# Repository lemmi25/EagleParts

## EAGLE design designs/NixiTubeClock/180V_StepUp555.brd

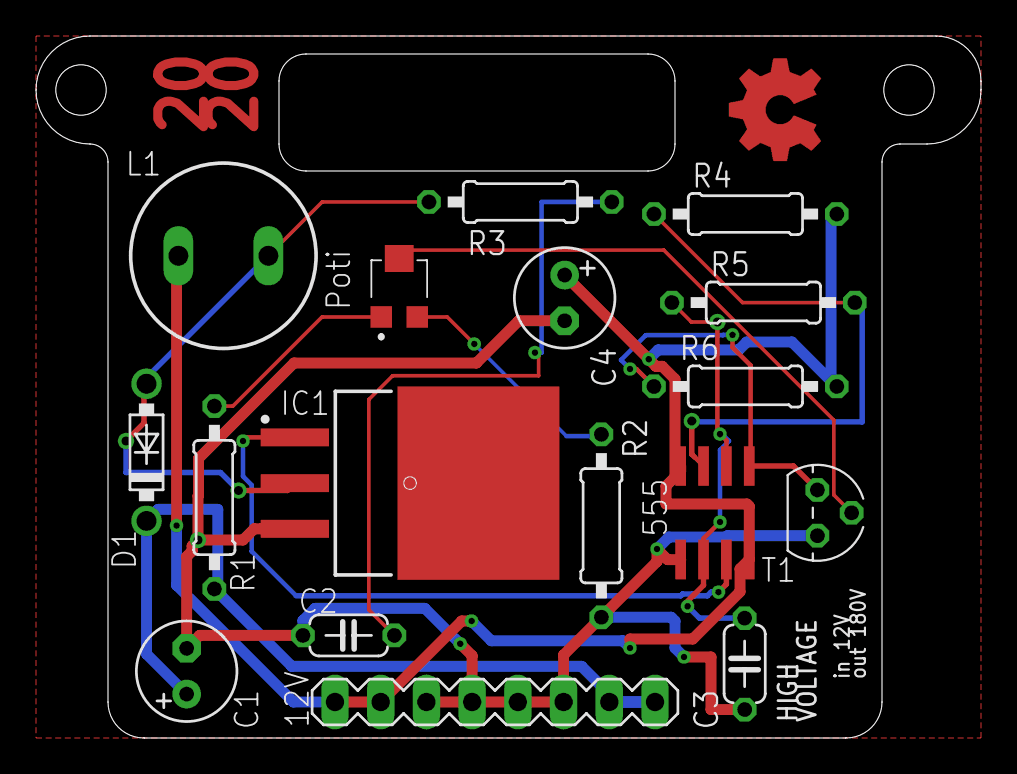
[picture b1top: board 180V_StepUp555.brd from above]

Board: 2 copper layers, 52.5 x 39.0 mm, 17 parts (0 on the bottom side), 12 nets.

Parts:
C1: 2.2uF; E2,5-6
C2: 100pF; C050-024X044
C3: 222; C050-024X044
C4: 330uF; E2,5-6
D1: UF4004; DO41-7.6
IC1: IRF740SPBF; TO254P1524X483-4N
IC2: LM555D; SO08
L1: SD12K100
R1: 220k; 0207/10
R2: 470R; 0207/10
R3: 2.2k; 0207/10
R4: 1k; 0207/10
R5: 10k; 0207/10
R6: 56k; 0207/10
SV2: MA08-1
T1: BC547; TO92
VR1: 1K; EVM3YSX50B14

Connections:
12V: C4.+, IC2.4, IC2.8, L1.2, R4.2, R6.2, SV2.1, SV2.2
+170V: C1.+, D1.C, R1.2, SV2.7, SV2.8
GND: C1.-, C2.2, C3.2, C4.-, IC1.3, IC2.1, R2.1, SV2.3, SV2.4, SV2.5, SV2.6, T1.1
unnamed: R2.2, VR1.C1
unnamed: R1.1, VR1.A1
unnamed: T1.2, VR1.B1
unnamed: D1.A, IC1.2, L1.1, R3.2
unnamed: IC2.5, R6.1, T1.3
unnamed: C2.1, R3.1
unnamed: C3.1, IC2.2, IC2.6, R5.1
unnamed: IC2.7, R4.1, R5.2
unnamed: IC1.1, IC2.3

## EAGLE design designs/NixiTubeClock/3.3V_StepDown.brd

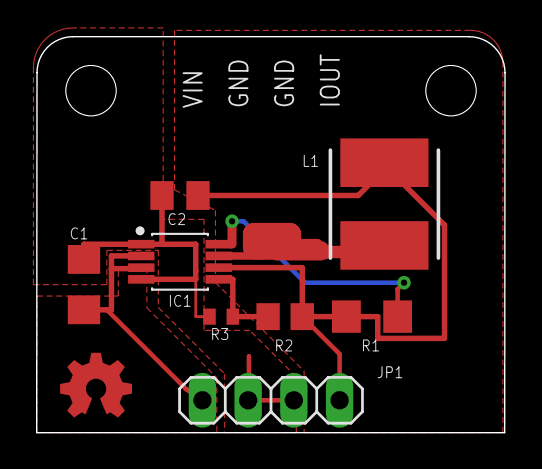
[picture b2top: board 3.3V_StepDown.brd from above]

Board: 2 copper layers, 26.0 x 22.0 mm, 8 parts (0 on the bottom side), 6 nets.

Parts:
C1: 10uF; C1206
C2: 22uF; C0805K
IC1: TPS62160DGKR; SOP65P490X110-8N
JP1: 1X04
L1: VLS6045EX-221M; INDPM6060X450N
R1: 100kOhm; R1206
R2: 562kOhm; R0805
R3: 180kOhm; R0402

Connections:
AGND: C1.2, C2.2, IC1.1, IC1.4, JP1.2, JP1.3, R3.1
FB2: IC1.5, R2.1, R3.2
IOUT: C2.1, IC1.6, JP1.4, L1.2, R1.2, R2.2
PG2: IC1.8, R1.1
SW2: IC1.7, L1.1
VIN: C1.1, IC1.2, IC1.3, JP1.1

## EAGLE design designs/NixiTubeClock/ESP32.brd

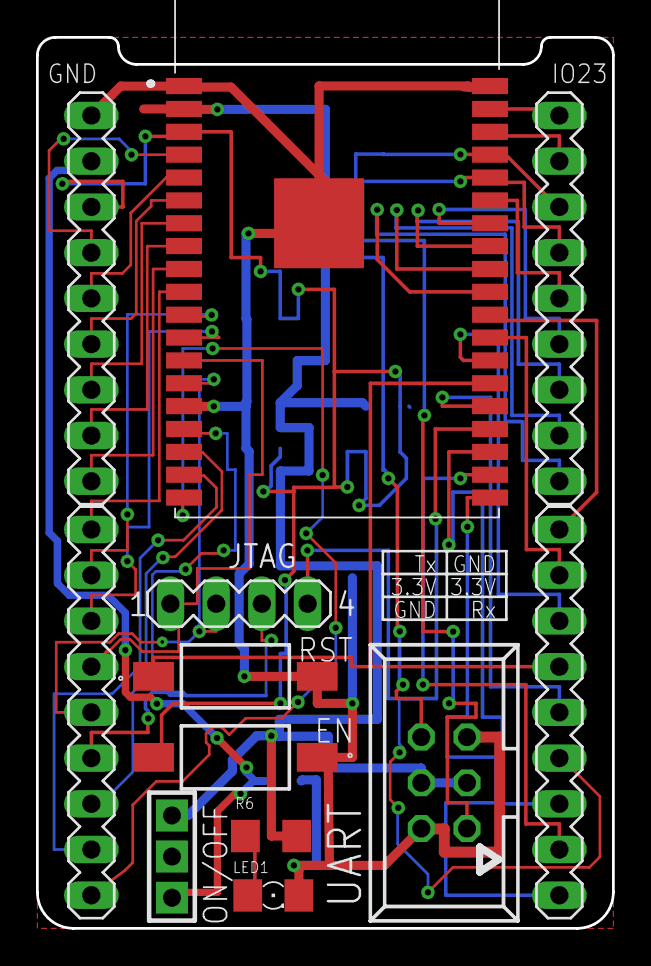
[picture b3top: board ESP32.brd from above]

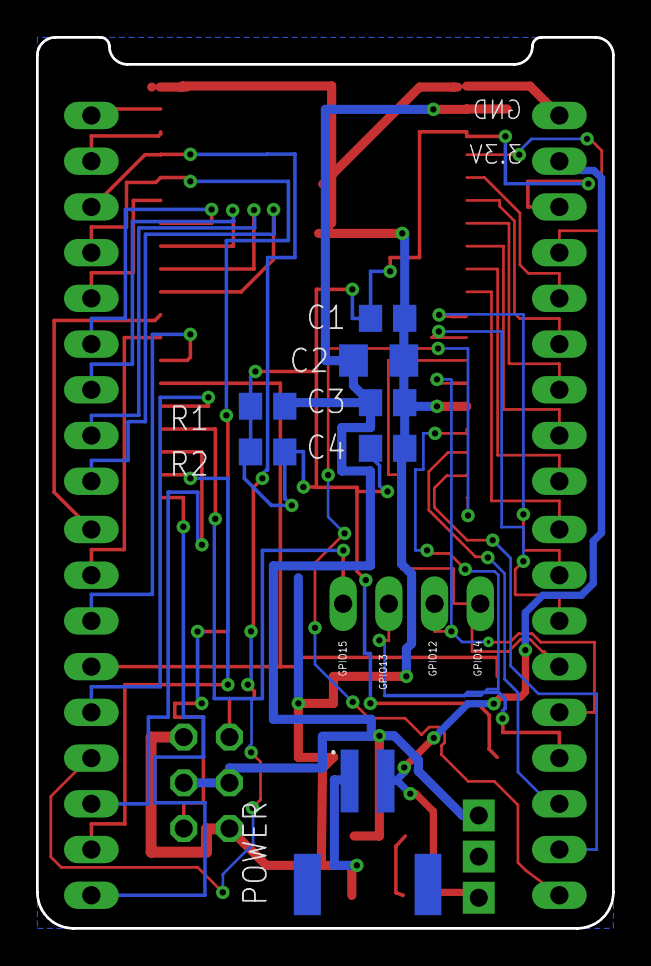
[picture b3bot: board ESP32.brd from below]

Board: 2 copper layers, 32.0 x 49.5 mm, 19 parts (7 on the bottom side), 38 nets.

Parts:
C1, C4: 1nF; C0805
C2: 100uF; C1206
C3: 1uF; C0805
EN: FSMSMTR; FSMSM
IC6: ESP32-WROVER-B; ESP32WROVERIB16MB
JTAG: 1; MA04-1
LED1: 1206
ON/OFF: -CON3; CON3
POWER: S2B-PH-SM4-TB; JST_S2B-PH-SM4-TB
R1: 12k; R0805
R2: 460ohm; R0805
R6: 1K; R1206
RST: FSMSMTR; FSMSM
SV1, SV2, SV5, SV6: MA09-1
UART: 057-006-1

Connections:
3.3V: C2.1, C3.1, IC6.2, ON/OFF.P$1, R1.2, R6.2, UART.3, UART.4
3.3V_IN: ON/OFF.P$3, POWER.2, SV5.8
CLK: IC6.20, SV1.9
CMD: IC6.19, SV6.1
EN: C1.1, C4.1, EN.2, IC6.3, R1.1, R2.1, R2.2, SV5.7
GND: C1.2, C2.2, C3.2, C4.2, EN.1, IC6.1, IC6.15, IC6.38, IC6.39, LED1.C, POWER.1, RST.2, SV5.9, UART.2, UART.5
GPIO12: IC6.14, JTAG.2, SV6.5
GPIO13: IC6.16, JTAG.3, SV6.4
GPIO14: IC6.13, JTAG.1, SV6.6
GPIO15: IC6.23, JTAG.4, SV1.6
IO0: IC6.25, RST.1, SV1.4
IO2: IC6.24, SV1.5
IO4: IC6.26, SV1.3
IO5: IC6.29, SV2.9
IO18: IC6.30, SV2.8
IO19: IC6.31, SV2.7
IO21: IC6.33, SV2.5
IO22: IC6.36, SV2.2
IO23: IC6.37, SV2.1
IO25: IC6.10, SV6.9
IO26: IC6.11, SV6.8
IO27: IC6.12, SV6.7
IO32: IC6.8, SV5.2
IO33: IC6.9, SV5.1
IO34: IC6.6, SV5.4
IO35: IC6.7, SV5.3
unnamed: LED1.A, R6.1
NC_1: IC6.27, SV1.2
NC_2: IC6.28, SV1.1
NC_3: IC6.32, SV2.6
RXD0: IC6.34, SV2.4, UART.1
SD0: IC6.21, SV1.8
SD1: IC6.22, SV1.7
SD2: IC6.17, SV6.3
SD3: IC6.18, SV6.2
SEN_VN: IC6.5, SV5.5
SEN_VP: IC6.4, SV5.6
TXD0: IC6.35, SV2.3, UART.6

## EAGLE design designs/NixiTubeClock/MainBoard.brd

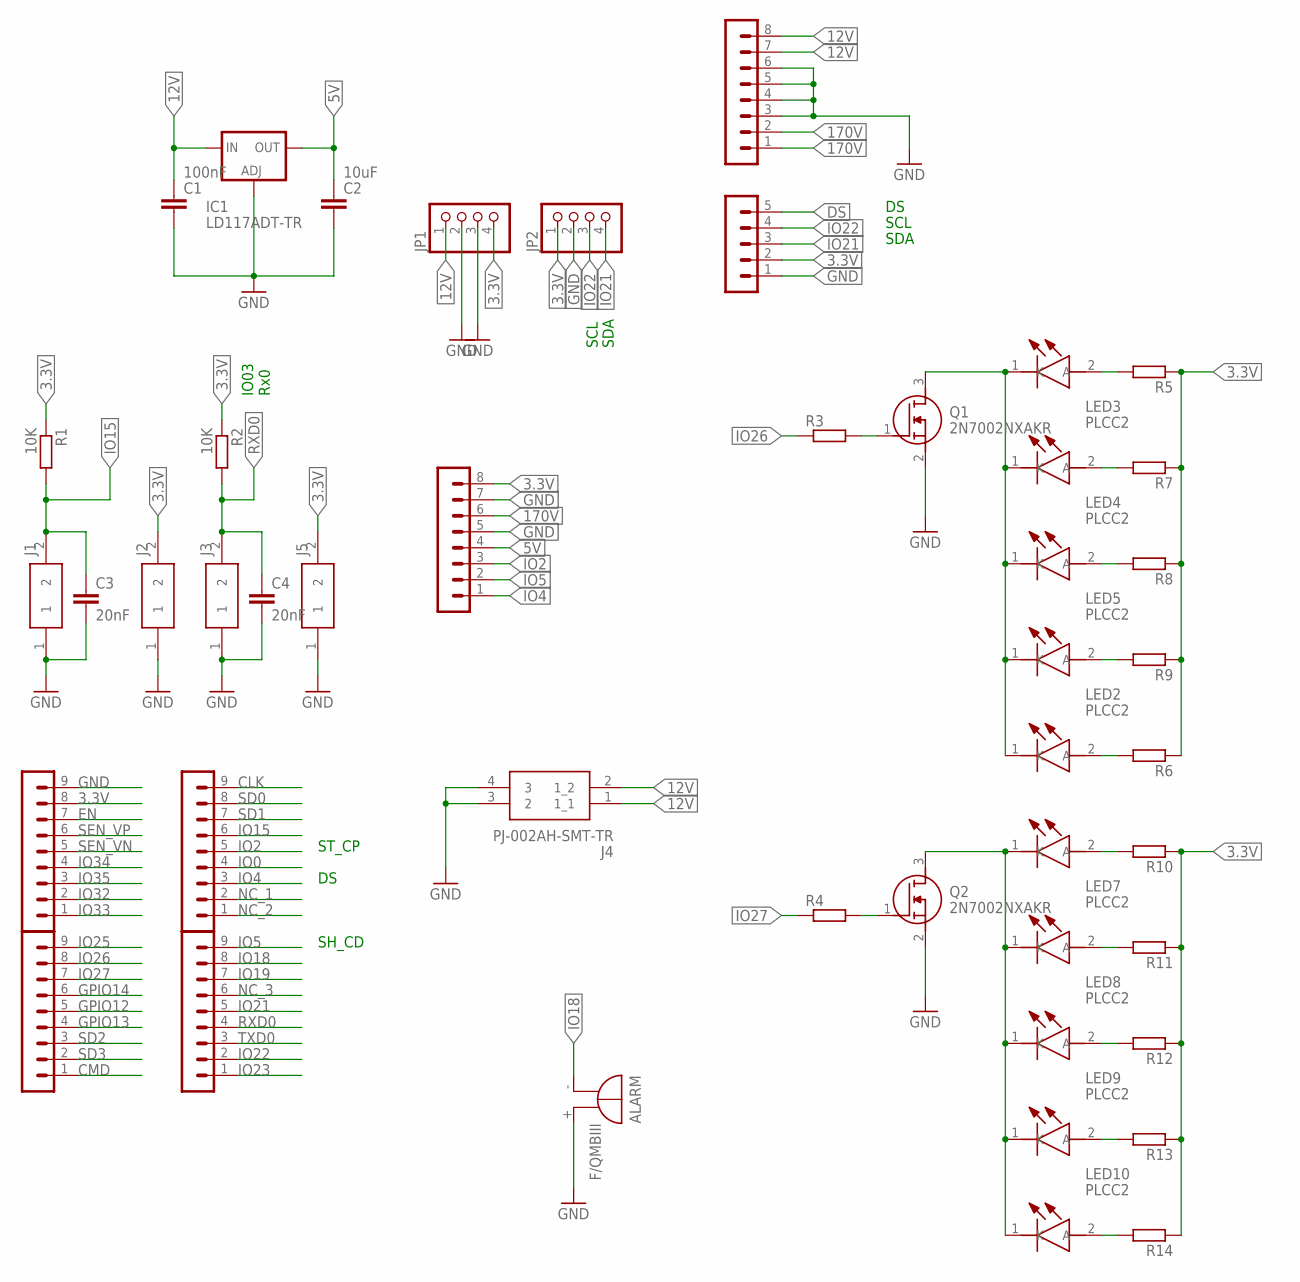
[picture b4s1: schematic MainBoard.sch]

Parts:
ALARM: F/QMBIII
C1: 100nF; C1206
C2: 10uF; C1206
C3, C4: 20nF; C0805
IC1: LD117ADT-TR; DPACK
J1, J2, J3, J5: S2B-NSHSS-TB; SM02B-NSHSS-TB
J4: PJ-002AH-SMT-TR
JP1, JP2: PINHD-1X4; 1X04
LED1, LED2, LED3, LED4, LED5, LED6, LED7, LED8, LED9, LED10: PLCC2; LEDM3528X200N
Q1, Q2: 2N7002NXAKR; SOT95P230X110-3N
R1, R2: 10K; R1206
R3, R4, R5, R6, R7, R8, R9, R10, R11, R12, R13, R14: R-EU_1206R1206; R1206
SV1, SV7: PINHEADER-1X8; MA08-1
SV2, SV3, SV4, SV5: PINHEADER-1X9; MA09-1
SV6: MA05-1

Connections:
3.3V: J2.2, J5.2, JP1.4, JP2.1, R1.1, R2.1, R5.1, R6.1, R7.1, R8.1, R9.1, R10.1, R11.1, R12.1, R13.1, R14.1, SV1.8, SV2.8, SV6.2
5V: C2.1, IC1.4 (OUT), SV1.4
12V: C1.1, IC1.3 (IN), J4.1 (1_1), J4.2 (1_2), JP1.1, SV7.7, SV7.8
170V: SV1.6, SV7.1, SV7.2
CLK: SV4.9
CMD: SV3.1
DS: SV6.5
EN: SV2.7
GND: ALARM.+ (-), C1.2, C2.2, C3.2, C4.2, IC1.1 (ADJ), J1.1, J2.1, J3.1, J4.3 (2), J4.4 (3), J5.1, JP1.2, JP1.3, JP2.2, Q1.2 (S), Q2.2 (S), SV1.5, SV1.7, SV2.9, SV6.1, SV7.3, SV7.4, SV7.5, SV7.6
GND_LED_BTM: LED6.1 (K), LED7.1 (K), LED8.1 (K), LED9.1 (K), LED10.1 (K), Q2.3 (D)
GND_LED_TOP: LED1.1 (K), LED2.1 (K), LED3.1 (K), LED4.1 (K), LED5.1 (K), Q1.3 (D)
GPIO12: SV3.5
GPIO13: SV3.4
GPIO14: SV3.6
IO0: SV4.4
IO2: SV1.3, SV4.5
IO4: SV1.1, SV4.3
IO5: SV1.2, SV5.9
IO15: C3.1, J1.2, R1.2, SV4.6
IO18: ALARM.- (+), SV5.8
IO19: SV5.7
IO21: JP2.4, SV5.5, SV6.3
IO22: JP2.3, SV5.2, SV6.4
IO23: SV5.1
IO25: SV3.9
IO26: R3.1, SV3.8
IO27: R4.1, SV3.7
IO32: SV2.2
IO33: SV2.1
IO34: SV2.4
IO35: SV2.3
unnamed: Q1.1 (G), R3.2
unnamed: LED1.2 (A), R5.2
unnamed: LED3.2 (A), R7.2
unnamed: LED4.2 (A), R8.2
unnamed: LED5.2 (A), R9.2
unnamed: LED2.2 (A), R6.2
unnamed: Q2.1 (G), R4.2
unnamed: LED6.2 (A), R10.2
unnamed: LED7.2 (A), R11.2
unnamed: LED8.2 (A), R12.2
unnamed: LED9.2 (A), R13.2
unnamed: LED10.2 (A), R14.2
NC_1: SV4.2
NC_2: SV4.1
NC_3: SV5.6
RXD0: C4.1, J3.2, R2.2, SV5.4
SD0: SV4.8
SD1: SV4.7
SD2: SV3.3
SD3: SV3.2
SEN_VN: SV2.5
SEN_VP: SV2.6
TXD0: SV5.3

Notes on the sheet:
ST_CP
SH_CD
SCL
SDA
IO03 Rx0

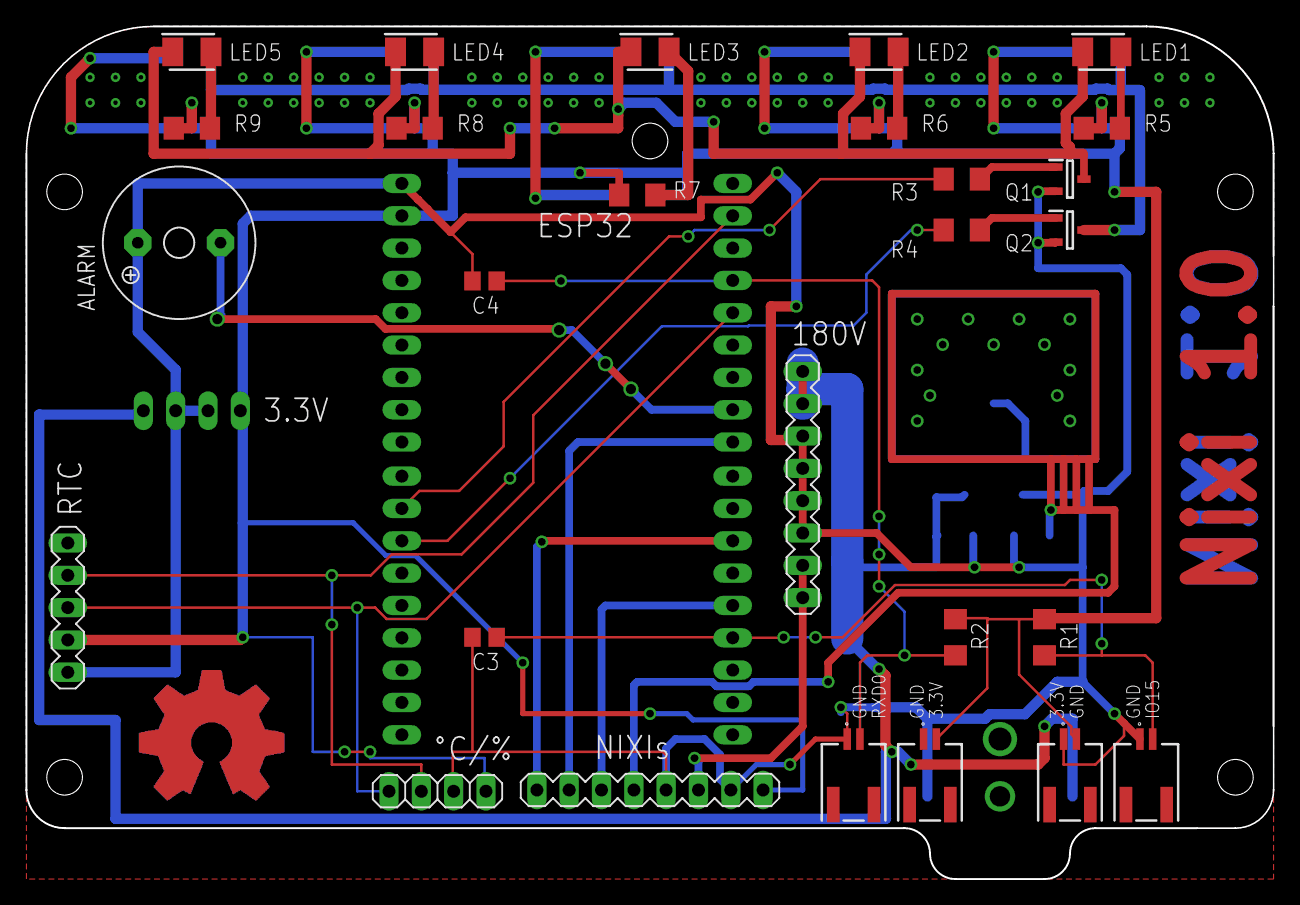
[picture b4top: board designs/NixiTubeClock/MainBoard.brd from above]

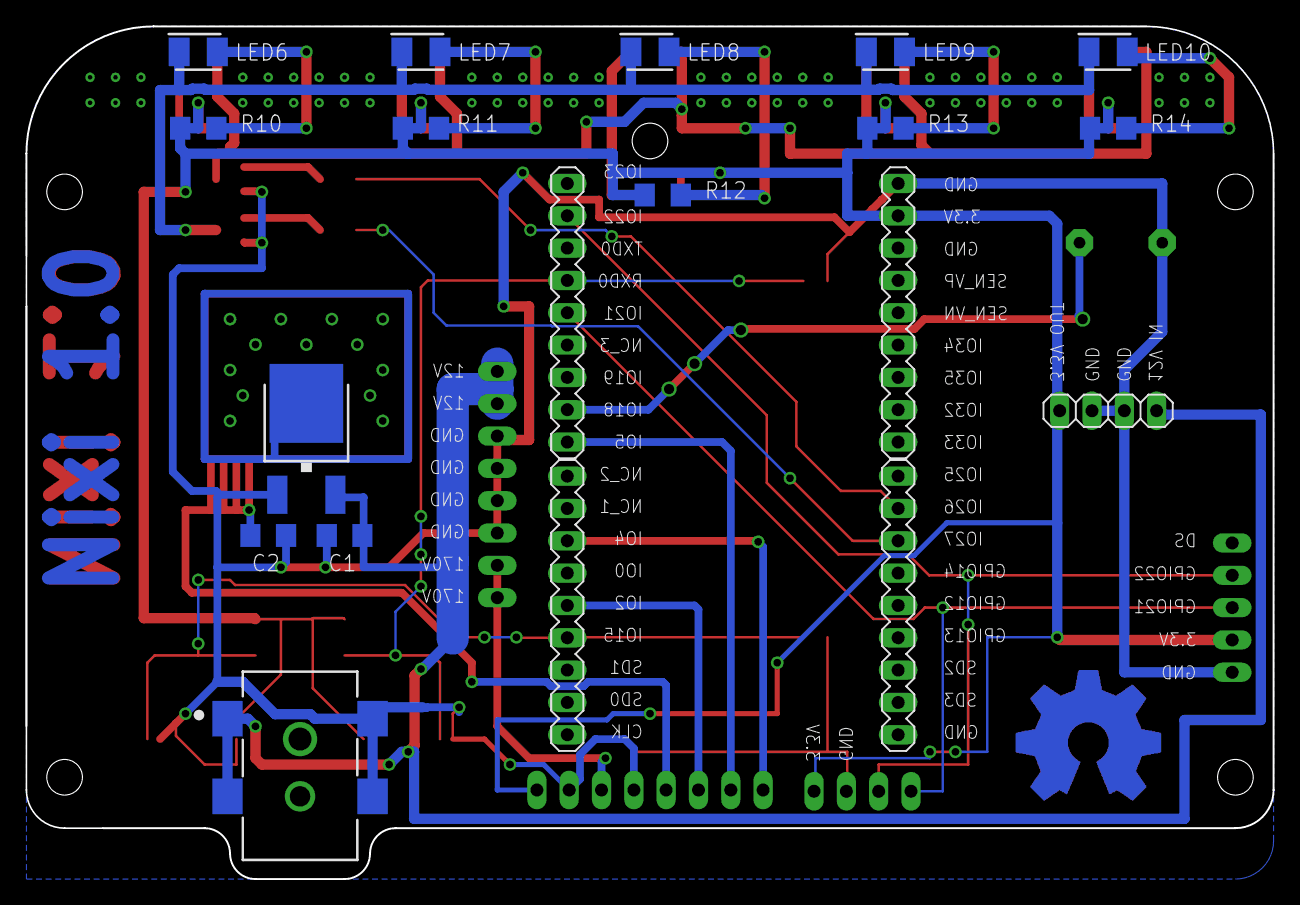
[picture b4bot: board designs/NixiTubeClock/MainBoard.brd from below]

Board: 2 copper layers, 98.0 x 67.0 mm, 46 parts (19 on the bottom side), 29 nets.

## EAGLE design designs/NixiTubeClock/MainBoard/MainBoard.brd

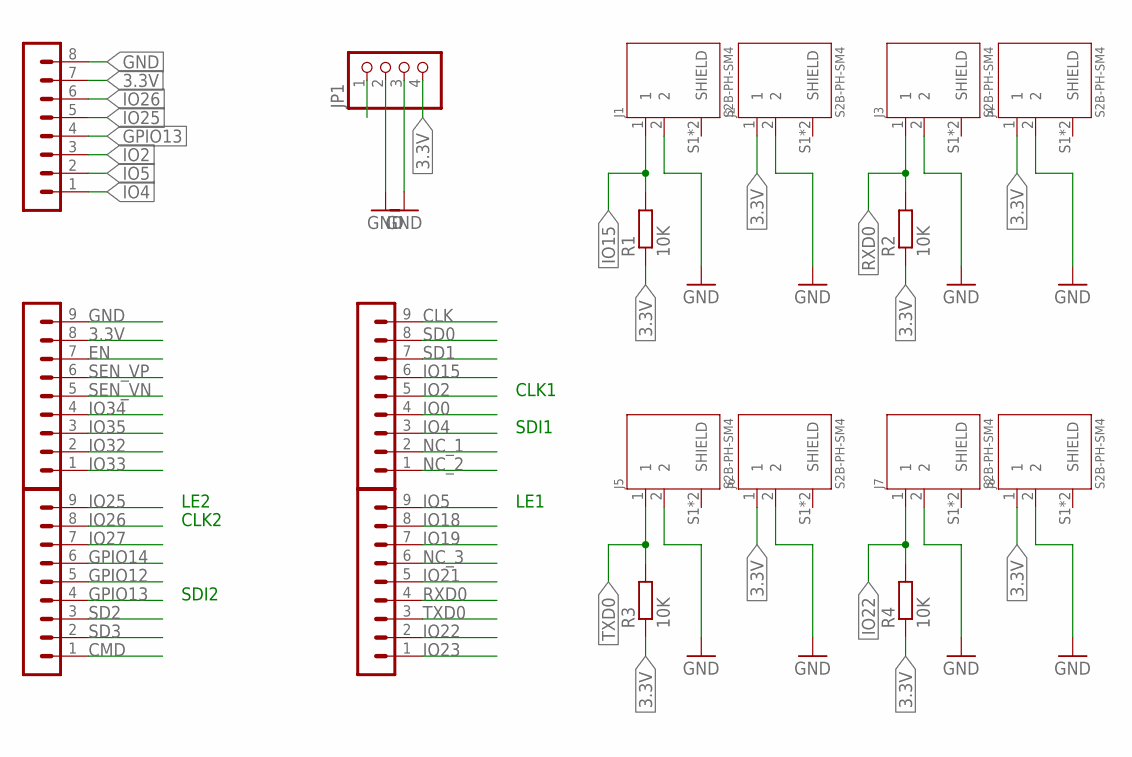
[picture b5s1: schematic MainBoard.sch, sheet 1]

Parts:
J1, J2, J3, J4, J5, J6, J7, J8: S2B-PH-SM4; JST_S2B-PH-SM4-TB(LF)(SN)
JP1: PINHD-1X4; 1X04
R1, R2, R3, R4: 10K; R1206
SV2, SV3, SV5, SV6: PINHEADER-1X9; MA09-1
SV4: PINHEADER-1X8; MA08-1

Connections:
3.3V: J2.1, J4.1, J6.1, J8.1, JP1.4, R1.1, R2.1, R3.1, R4.1, SV4.7, SV5.8
CLK: SV2.9
CMD: SV6.1
EN: SV5.7
GND: J1.2, J2.2, J3.2, J4.2, J5.2, J6.2, J7.2, J8.2, JP1.2, JP1.3, SV4.8, SV5.9
GPIO12: SV6.5
GPIO13: SV4.4, SV6.4
GPIO14: SV6.6
IO0: SV2.4
IO2: SV2.5, SV4.3
IO4: SV2.3, SV4.1
IO5: SV3.9, SV4.2
IO15: J1.1, R1.2, SV2.6
IO18: SV3.8
IO19: SV3.7
IO21: SV3.5
IO22: J7.1, R4.2, SV3.2
IO23: SV3.1
IO25: SV4.5, SV6.9
IO26: SV4.6, SV6.8
IO27: SV6.7
IO32: SV5.2
IO33: SV5.1
IO34: SV5.4
IO35: SV5.3
NC: JP1.1
NC_1: SV2.2
NC_2: SV2.1
NC_3: SV3.6
RXD0: J3.1, R2.2, SV3.4
SD0: SV2.8
SD1: SV2.7
SD2: SV6.3
SD3: SV6.2
SEN_VN: SV5.5
SEN_VP: SV5.6
TXD0: J5.1, R3.2, SV3.3

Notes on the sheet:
CLK1
CLK2
LE1
LE2
SDI1
SDI2

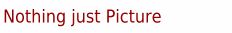
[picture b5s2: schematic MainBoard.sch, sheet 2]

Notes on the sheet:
Nothing just Picture

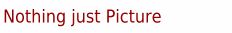
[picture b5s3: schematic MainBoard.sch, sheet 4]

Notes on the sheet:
Nothing just Picture

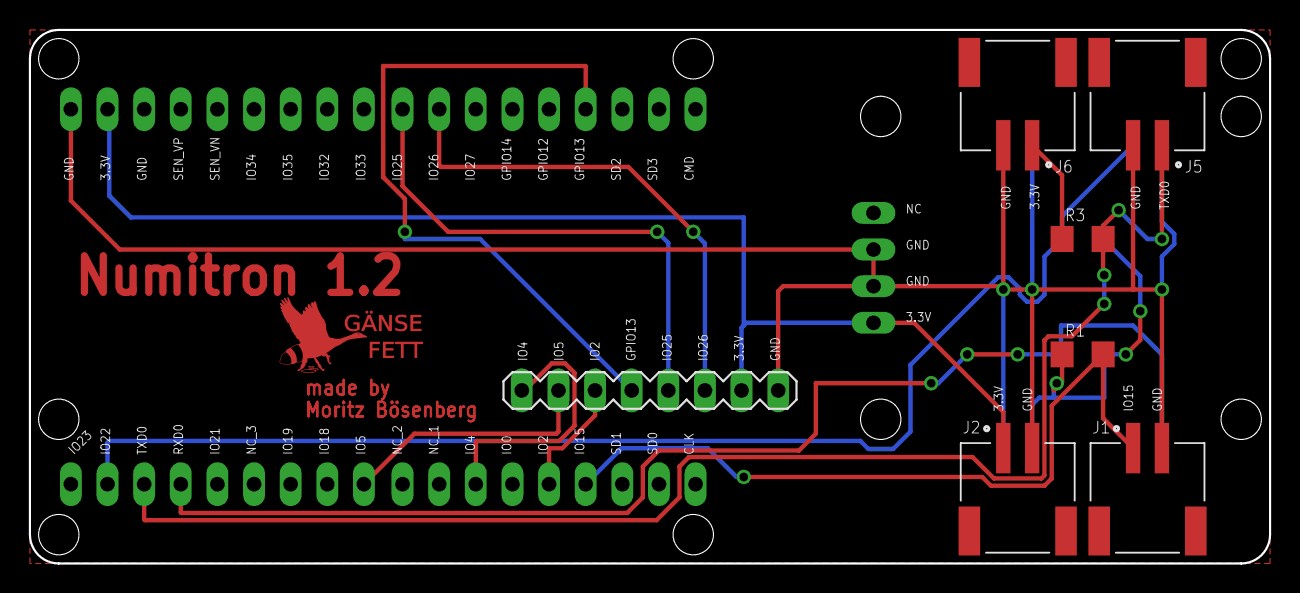
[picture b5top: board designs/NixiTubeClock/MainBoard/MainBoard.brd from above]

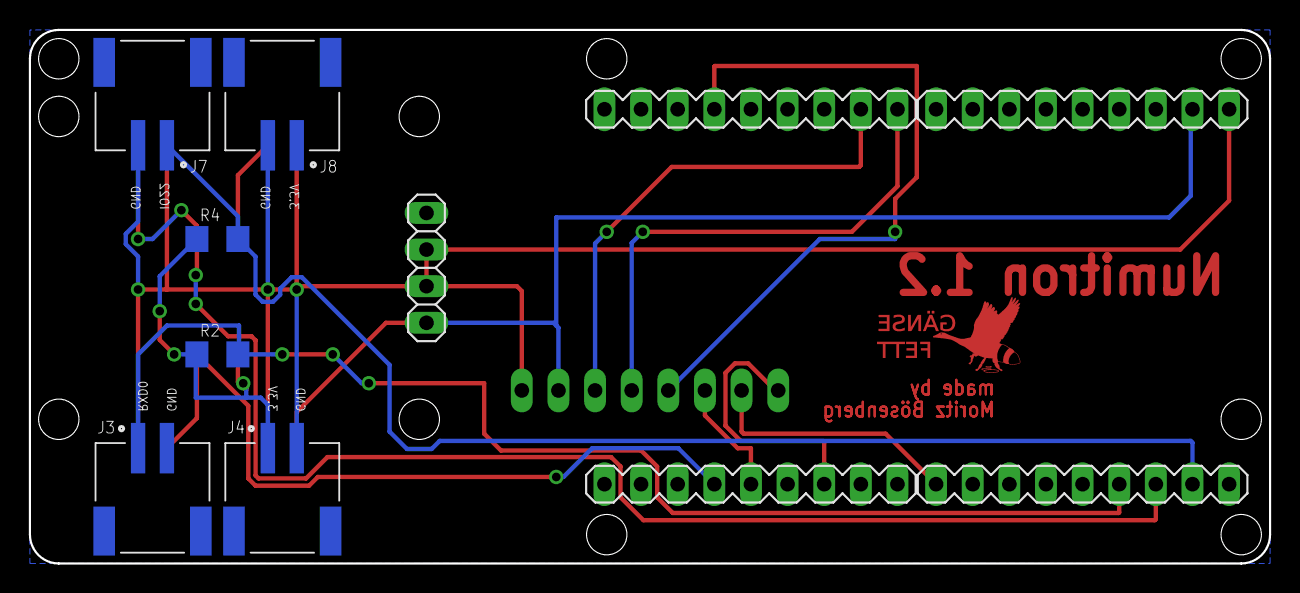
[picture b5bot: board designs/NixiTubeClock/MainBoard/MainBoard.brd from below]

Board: 2 copper layers, 86.0 x 37.0 mm, 18 parts (11 on the bottom side), 12 nets.

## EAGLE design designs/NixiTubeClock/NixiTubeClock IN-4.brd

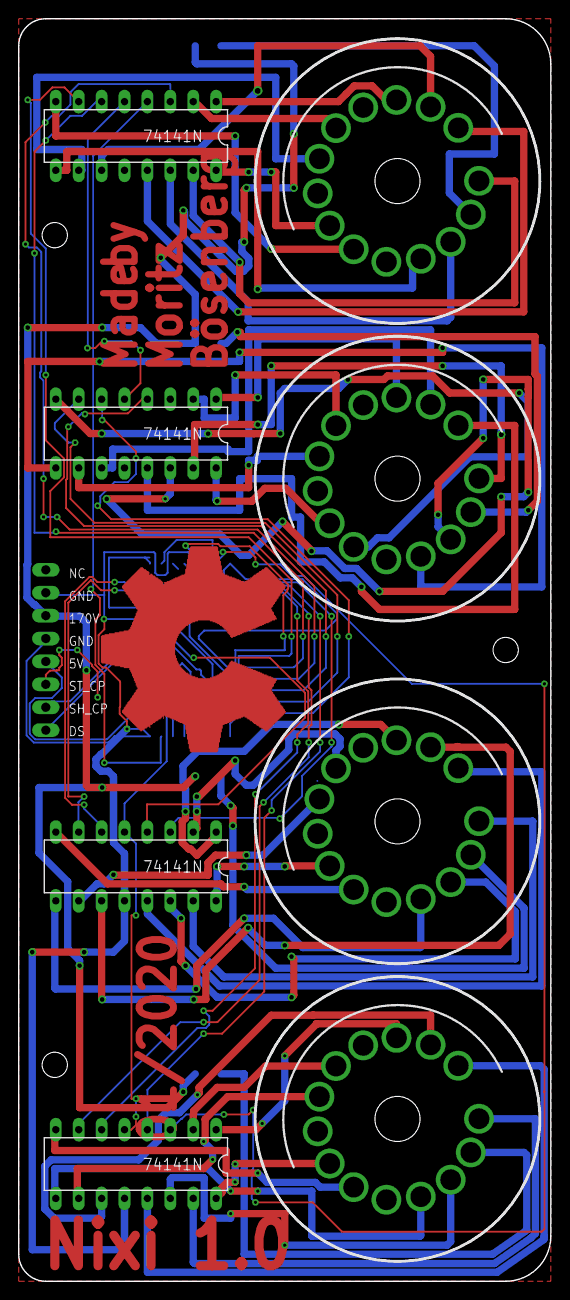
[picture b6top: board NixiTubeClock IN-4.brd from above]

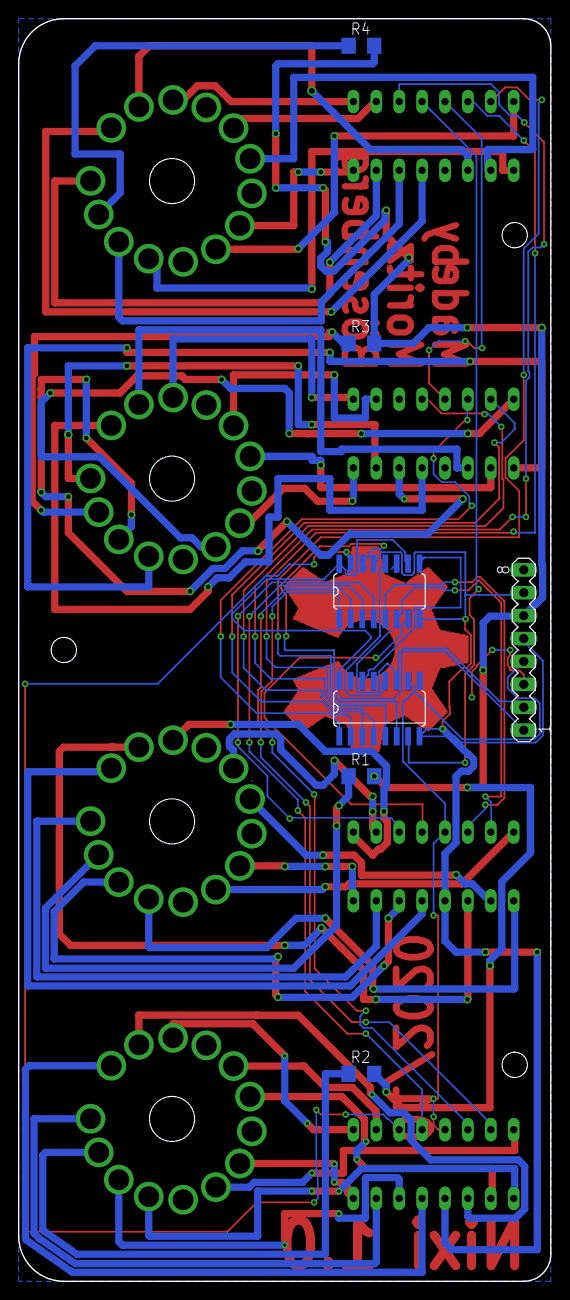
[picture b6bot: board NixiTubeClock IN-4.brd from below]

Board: 2 copper layers, 59.0 x 140.0 mm, 15 parts (7 on the bottom side), 67 nets.

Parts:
IC1, IC3, IC4, IC6: 74141N; DIL16
IC2, IC5: 74HCT595D; SO16
N1, N2, N3, N4: IN-4; IN-18
R1, R2, R3, R4: 12k; R1206
SV1: MA08-1

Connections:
5V: IC1.5, IC2.10, IC2.16, IC3.5, IC4.5, IC5.10, IC5.16, IC6.5, SV1.4
170V: R1.2, R2.2, R3.2, R4.2, SV1.6
DRIVER_0_0: IC1.16, N1.N/C2
DRIVER_0_1: IC3.16, N2.N/C2
DRIVER_0_2: IC4.16, N3.N/C2
DRIVER_0_3: IC6.16, N4.N/C2
DRIVER_1_0: IC1.15, N1.9
DRIVER_1_1: IC3.15, N2.9
DRIVER_1_2: IC4.15, N3.9
DRIVER_1_3: IC6.15, N4.9
DRIVER_2_0: IC1.8, N1.8
DRIVER_2_1: IC3.8, N2.8
DRIVER_2_2: IC4.8, N3.8
DRIVER_2_3: IC6.8, N4.8
DRIVER_3_0: IC1.9, N1.1
DRIVER_3_1: IC3.9, N2.1
DRIVER_3_2: IC4.9, N3.1
DRIVER_3_3: IC6.9, N4.1
DRIVER_4_0: IC1.13, N1.N/C
DRIVER_4_1: IC3.13, N2.N/C
DRIVER_4_2: IC4.13, N3.N/C
DRIVER_4_3: IC6.13, N4.N/C
DRIVER_5_0: IC1.14, N1.A2
DRIVER_5_1: IC3.14, N2.A2
DRIVER_5_2: IC4.14, N3.A2
DRIVER_5_3: IC6.14, N4.A2
DRIVER_6_0: IC1.11, N1.4
DRIVER_6_1: IC3.11, N2.4
DRIVER_6_2: IC4.11, N3.4
DRIVER_6_3: IC6.11, N4.4
DRIVER_7_0: IC1.10, N1.7
DRIVER_7_1: IC3.10, N2.7
DRIVER_7_2: IC4.10, N3.7
DRIVER_7_3: IC6.10, N4.7
DRIVER_8_0: IC1.1, N1.5
DRIVER_8_1: IC3.1, N2.5
DRIVER_8_2: IC4.1, N3.5
DRIVER_8_3: IC6.1, N4.5
DRIVER_9_0: IC1.2, N1.6
DRIVER_9_1: IC3.2, N2.6
DRIVER_9_2: IC4.2, N3.6
DRIVER_9_3: IC6.2, N4.6
DS: IC2.14, SV1.1
GND: IC1.12, IC2.8, IC2.13, IC3.12, IC4.12, IC5.8, IC5.13, IC6.12, SV1.5, SV1.7
unnamed: IC4.4, IC5.3
unnamed: N2.0, R1.1
unnamed: N3.0, R3.1
unnamed: N4.0, R4.1
unnamed: N1.0, R2.1
unnamed: IC1.3, IC2.15
unnamed: IC1.6, IC2.1
unnamed: IC1.7, IC2.2
unnamed: IC1.4, IC2.3
unnamed: IC2.4, IC3.3
unnamed: IC2.5, IC3.6
unnamed: IC2.6, IC3.7
unnamed: IC2.7, IC3.4
unnamed: IC4.3, IC5.15
unnamed: IC4.6, IC5.1
unnamed: IC4.7, IC5.2
unnamed: IC5.4, IC6.3
unnamed: IC5.5, IC6.6
unnamed: IC5.6, IC6.7
unnamed: IC5.7, IC6.4
SHIFT_DATA: IC2.9, IC5.14
SH_CP: IC2.11, IC5.11, SV1.2
ST_CP: IC2.12, IC5.12, SV1.3

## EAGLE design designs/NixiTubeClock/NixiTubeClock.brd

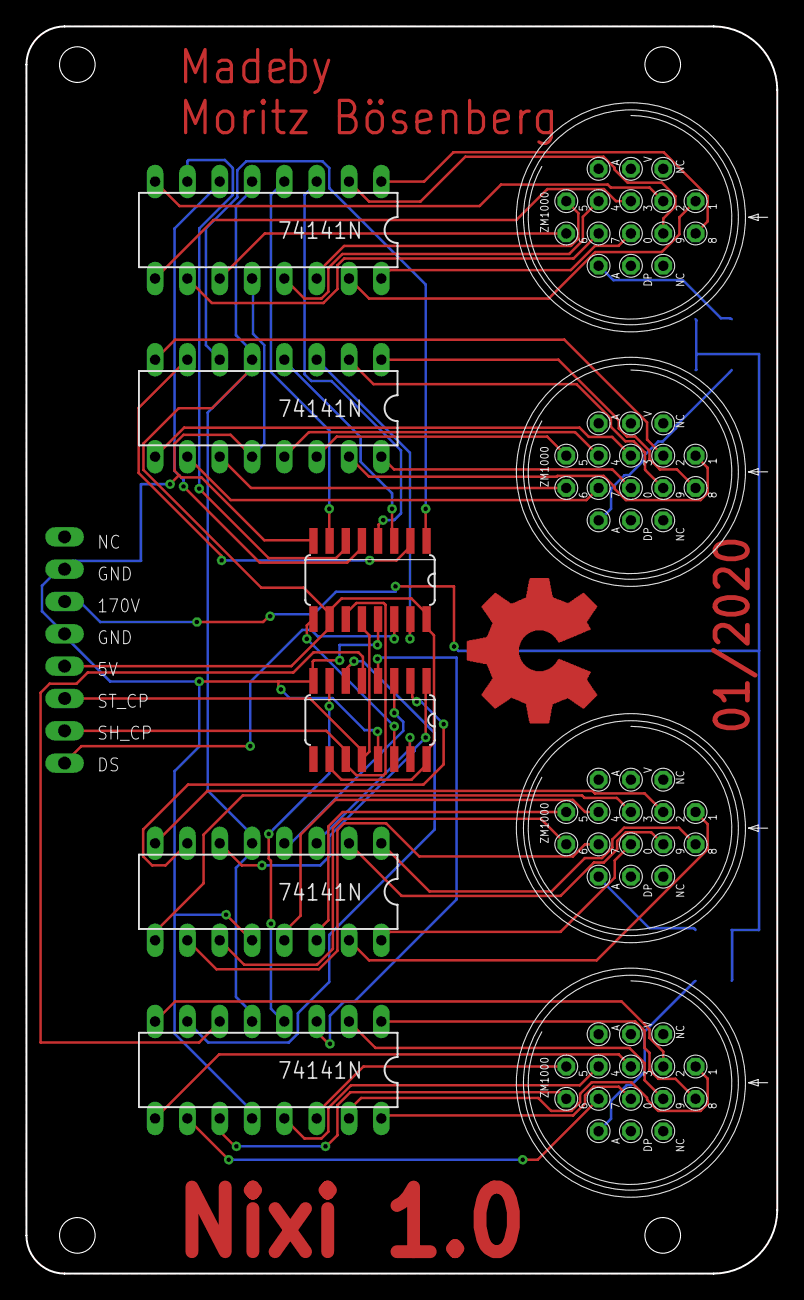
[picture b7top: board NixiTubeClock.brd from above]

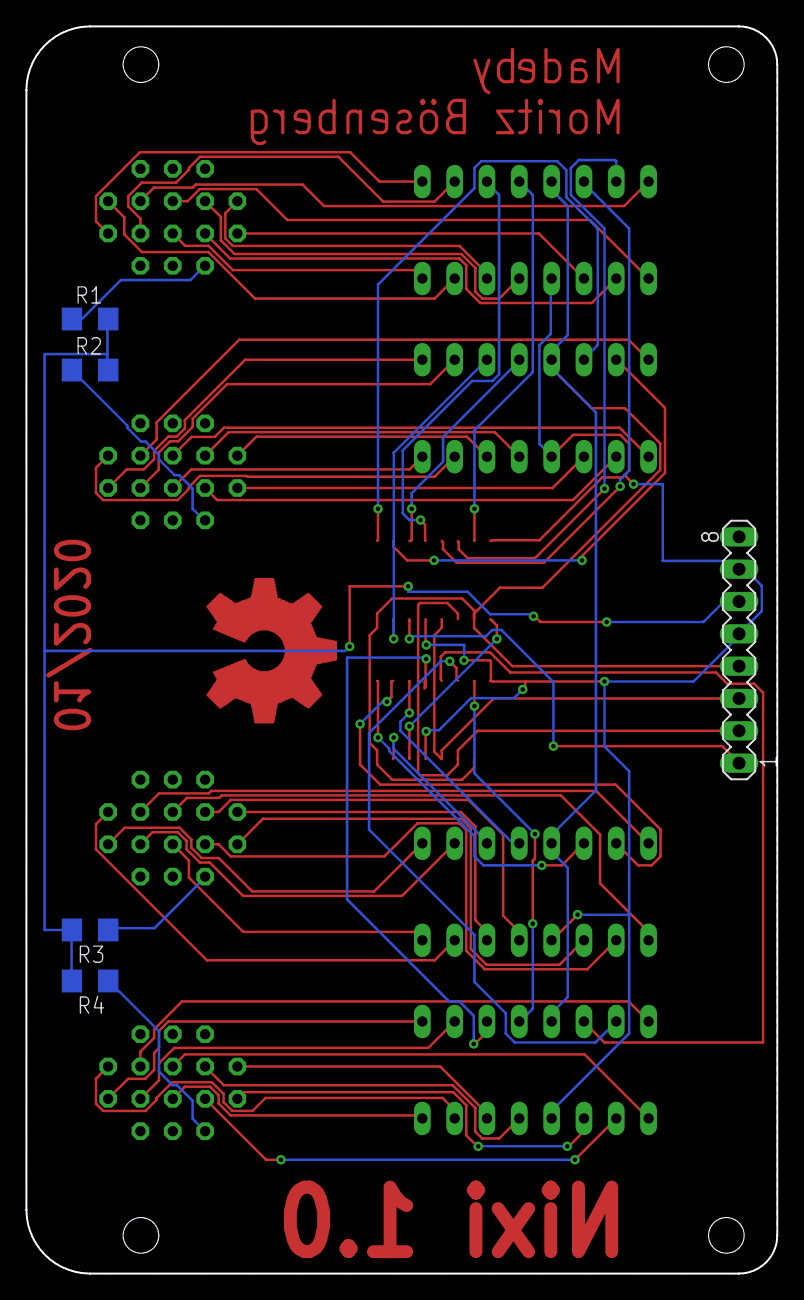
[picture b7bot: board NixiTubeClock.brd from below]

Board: 2 copper layers, 59.0 x 98.0 mm, 15 parts (5 on the bottom side), 67 nets.

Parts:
AN1, AN2, AN3, AN4: ZM1000
IC1, IC3, IC4, IC6: 74141N; DIL16
IC2, IC5: 74HCT595D; SO16
R1, R2, R3, R4: 12k; R1206
SV1: MA08-1

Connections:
5V: IC1.5, IC2.10, IC2.16, IC3.5, IC4.5, IC5.10, IC5.16, IC6.5, SV1.4
170V: R1.2, R2.2, R3.2, R4.2, SV1.6
DS: IC2.14, SV1.1
GND: IC1.12, IC2.8, IC2.13, IC3.12, IC4.12, IC5.8, IC5.13, IC6.12, SV1.5, SV1.7
unnamed: IC4.4, IC5.3
unnamed: AN1.0, IC1.16
unnamed: AN1.1, IC1.15
unnamed: AN1.2, IC1.8
unnamed: AN1.3, IC1.9
unnamed: AN1.4, IC1.13
unnamed: AN1.5, IC1.14
unnamed: AN1.6, IC1.11
unnamed: AN1.7, IC1.10
unnamed: AN1.8, IC1.1
unnamed: AN1.9, IC1.2
unnamed: AN2.0, IC3.16
unnamed: AN2.1, IC3.15
unnamed: AN2.2, IC3.8
unnamed: AN2.3, IC3.9
unnamed: AN2.4, IC3.13
unnamed: AN2.5, IC3.14
unnamed: AN2.6, IC3.11
unnamed: AN2.7, IC3.10
unnamed: AN2.8, IC3.1
unnamed: AN2.9, IC3.2
unnamed: AN3.0, IC4.16
unnamed: AN3.1, IC4.15
unnamed: AN3.2, IC4.8
unnamed: AN3.3, IC4.9
unnamed: AN3.4, IC4.13
unnamed: AN3.5, IC4.14
unnamed: AN3.6, IC4.11
unnamed: AN3.7, IC4.10
unnamed: AN3.8, IC4.1
unnamed: AN3.9, IC4.2
unnamed: AN4.0, IC6.16
unnamed: AN4.1, IC6.15
unnamed: AN4.2, IC6.8
unnamed: AN4.3, IC6.9
unnamed: AN4.4, IC6.13
unnamed: AN4.5, IC6.14
unnamed: AN4.6, IC6.11
unnamed: AN4.7, IC6.10
unnamed: AN4.8, IC6.1
unnamed: AN4.9, IC6.2
unnamed: AN1.A, R2.1
unnamed: AN2.A, R1.1
unnamed: AN3.A, R3.1
unnamed: AN4.A, R4.1
unnamed: IC1.3, IC2.15
unnamed: IC1.6, IC2.1
unnamed: IC1.7, IC2.2
unnamed: IC1.4, IC2.3
unnamed: IC2.4, IC3.3
unnamed: IC2.5, IC3.6
unnamed: IC2.6, IC3.7
unnamed: IC2.7, IC3.4
unnamed: IC4.3, IC5.15
unnamed: IC4.6, IC5.1
unnamed: IC4.7, IC5.2
unnamed: IC5.4, IC6.3
unnamed: IC5.5, IC6.6
unnamed: IC5.6, IC6.7
unnamed: IC5.7, IC6.4
SHIFT_DATA: IC2.9, IC5.14
SH_CP: IC2.11, IC5.11, SV1.2
ST_CP: IC2.12, IC5.12, SV1.3

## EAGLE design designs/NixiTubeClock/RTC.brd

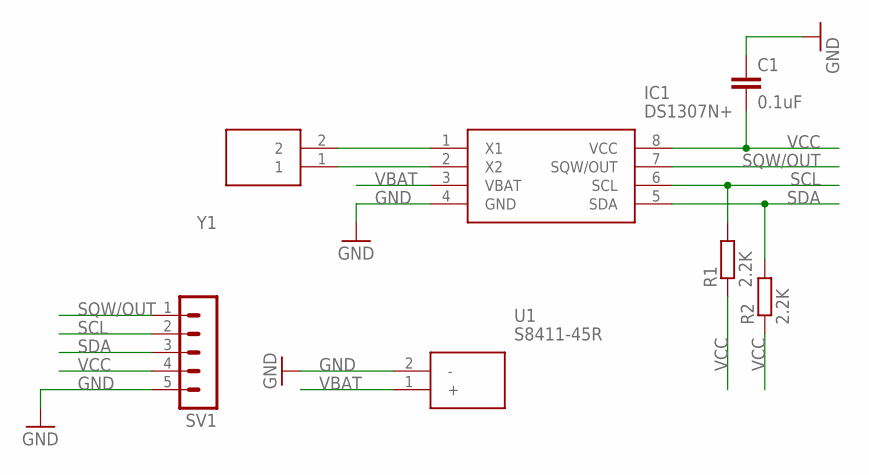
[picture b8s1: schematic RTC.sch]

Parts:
C1: 0.1uF; C0805
IC1: DS1307N+; DIP762W56P254L938H457Q8N
R1, R2: 2.2K; M1206
SV1: MA05-1
U1: S8411-45R; S8411-45R_1
Y1: CM7V-T1A-32.768K-9PF-20PPM-TA-; CM7VT1A32768KHZ125PF10PPMTBQC

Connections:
GND: C1.1, IC1.4 (GND), SV1.5, U1.2 (-)
unnamed: IC1.1 (X1), Y1.2
unnamed: IC1.2 (X2), Y1.1
SCL: IC1.6 (SCL), R1.2, SV1.2
SDA: IC1.5 (SDA), R2.2, SV1.3
SQW/OUT: IC1.7 (SQW/OUT), SV1.1
VBAT: IC1.3 (VBAT), U1.1 (+)
VCC: C1.2, IC1.8 (VCC), R1.1, R2.1, SV1.4

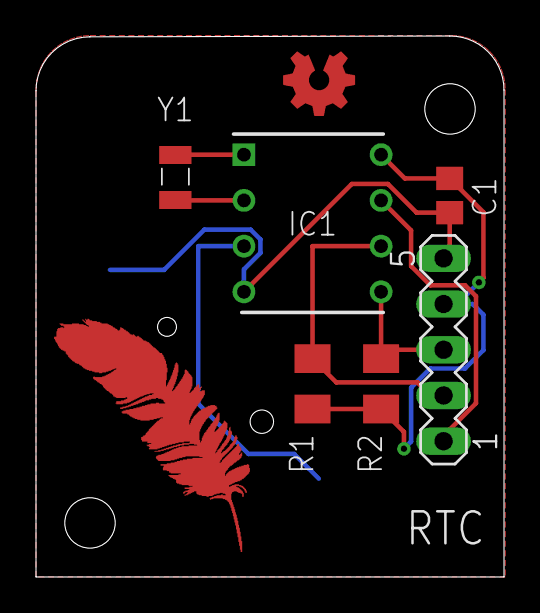
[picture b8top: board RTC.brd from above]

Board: 2 copper layers, 26.0 x 30.1 mm, 7 parts (1 on the bottom side), 8 nets.
